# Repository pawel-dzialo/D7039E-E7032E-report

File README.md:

# Report repo for courses D7039E, E7032E, HT22

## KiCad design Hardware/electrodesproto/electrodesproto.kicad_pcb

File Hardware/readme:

All the Hardware design and some simulation files.
The MCU_prototype is fully done with layout
Electrodes_proto is not done in layout preferably it should be done on a 4 layer PCB
but the capabilitys to create a PCB at the schools facilities makes it so It needs to be layed out using only two layer which makes it tough due to all power pins (V+ V-)

In the Simlulations:
Antialiasing,InsAmp,RCfilter is the main steps simulation individually
RC_amp_LP is the steps togheter
IN all sims not the exact components used in the circuitry have a simulation model so an equivalent part is used
but due to this the simulations are not 100% reliable and that why the main testing has been done in the lab.

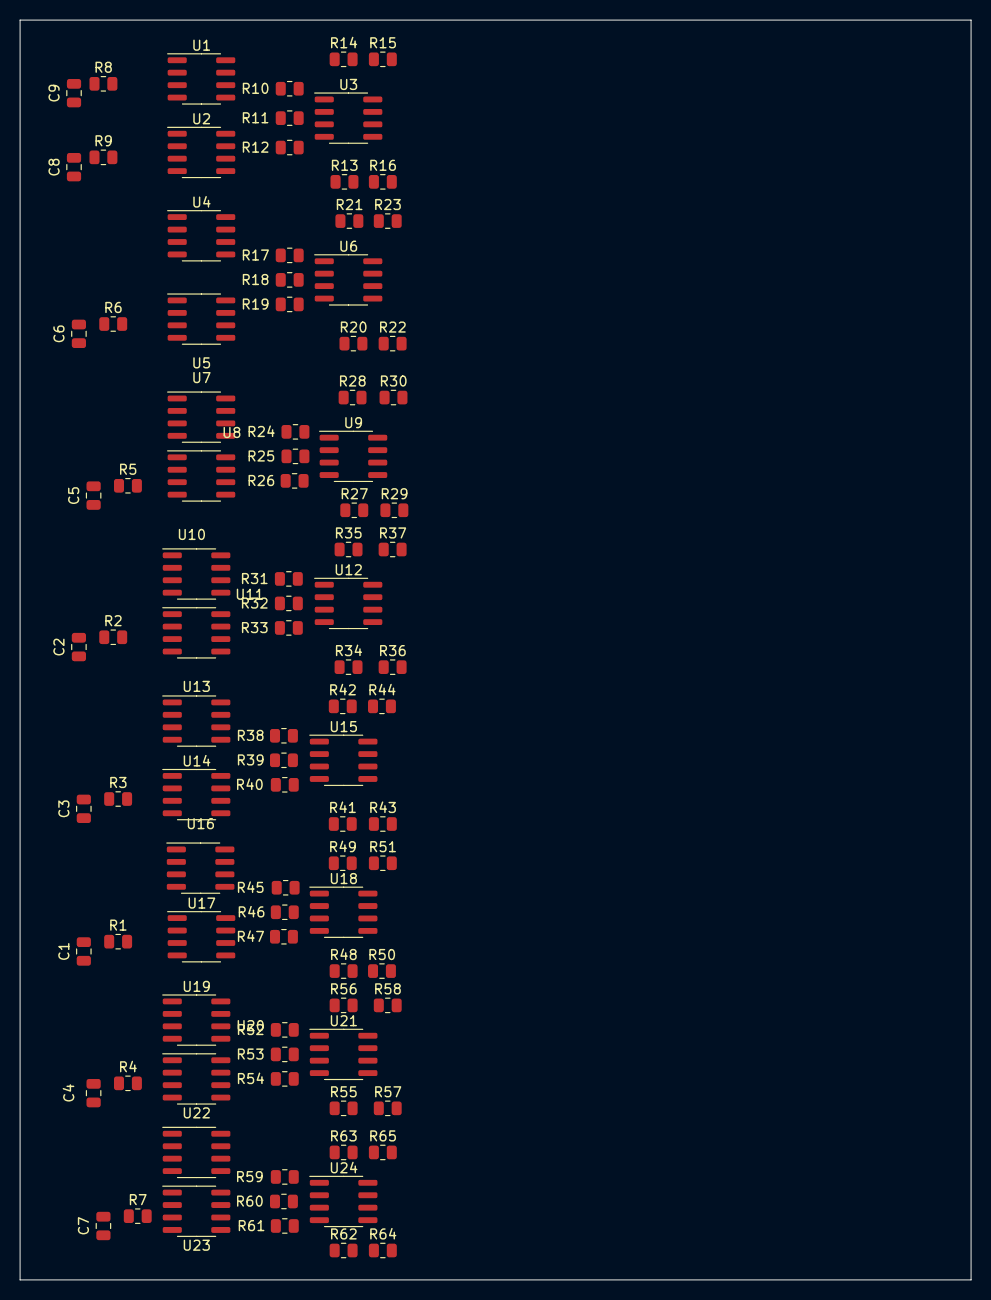
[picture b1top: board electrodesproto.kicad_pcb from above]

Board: 2 copper layers, 97.0 x 128.5 mm, 98 parts (0 on the bottom side), 68 nets, no tracks yet.

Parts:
C1, C2, C3, C4, C5, C6, C7, C8, C9: C; C_0805_2012Metric
R1, R2, R3, R4, R5, R6, R7, R8, R9, R13, R14, R15, R16, R20, R21, R22, R23, R27, R28, R29, R30, R34, R35, R36, R37, R41, R42, R43, R44, R48, R49, R50, R51, R55, R56, R57, R58, R62, R63, R64, R65: R; R_0805_2012Metric
R10, R11, R12, R17, R18, R19, R24, R25, R26, R31, R32, R33, R38, R39, R40, R45, R46, R47, R52, R53, R54, R59, R60, R61: R_Small; R_0805_2012Metric
U1, U2, U3, U4, U5, U6, U7, U8, U9, U10, U11, U12, U13, U14, U15, U16, U17, U18, U19, U20, U21, U22, U23, U24: OPA376xxD; SOIC-8_3.9x4.9mm_P1.27mm

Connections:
E_1: C8.1, R9.2, U2.3 (+)
E_2: C6.1, R6.2, U5.3 (+)
E_3: C5.1, R5.2, U8.3 (+)
E_4: C2.1, R2.2, U11.3 (+)
E_5: C3.1, R3.2, U14.3 (+)
E_6: C1.1, R1.2, U17.3 (+)
E_7: C4.1, R4.2, U20.3 (+)
E_8: C7.1, R7.2, U23.3 (+)
E_OUT_01: R16.2, U3.6
E_OUT_02: R22.2, U6.6
E_OUT_03: R29.2, U9.6
E_OUT_04: R36.2, U12.6
E_OUT_05: R43.2, U15.6
E_OUT_06: R50.2, U18.6
E_OUT_07: R57.2, U21.6
E_OUT_08: R64.2, U24.6
E_ref: C9.1, R8.2, U1.3 (+), U4.3 (+), U7.3 (+), U10.3 (+), U13.3 (+), U16.3 (+), U19.3 (+), U22.3 (+)
GND: C1.2, C2.2, C3.2, C4.2, C5.2, C6.2, C7.2, C8.2, C9.2, R15.2, R23.2, R30.2, R37.2, R44.2, R51.2, R58.2, R65.2
unnamed: R10.1, R14.1, U1.6
unnamed: R10.2, R11.1, U1.2 (-)
unnamed: R11.2, R12.1, U2.2 (-)
unnamed: R12.2, R13.1, U2.6
unnamed: R13.2, R16.1, U3.2 (-)
unnamed: R14.2, R15.1, U3.3 (+)
unnamed: R17.1, R21.1, U4.6
unnamed: R17.2, R18.1, U4.2 (-)
unnamed: R18.2, R19.1, U5.2 (-)
unnamed: R19.2, R20.1, U5.6
unnamed: R20.2, R22.1, U6.2 (-)
unnamed: R21.2, R23.1, U6.3 (+)
unnamed: R24.1, R28.1, U7.6
unnamed: R24.2, R25.1, U7.2 (-)
unnamed: R25.2, R26.1, U8.2 (-)
unnamed: R26.2, R27.1, U8.6
unnamed: R27.2, R29.1, U9.2 (-)
unnamed: R28.2, R30.1, U9.3 (+)
unnamed: R31.1, R35.1, U10.6
unnamed: R31.2, R32.1, U10.2 (-)
unnamed: R32.2, R33.1, U11.2 (-)
unnamed: R33.2, R34.1, U11.6
unnamed: R34.2, R36.1, U12.2 (-)
unnamed: R35.2, R37.1, U12.3 (+)
unnamed: R38.1, R42.1, U13.6
unnamed: R38.2, R39.1, U13.2 (-)
unnamed: R39.2, R40.1, U14.2 (-)
unnamed: R40.2, R41.1, U14.6
unnamed: R41.2, R43.1, U15.2 (-)
unnamed: R42.2, R44.1, U15.3 (+)
unnamed: R45.1, R49.1, U16.6
unnamed: R45.2, R46.1, U16.2 (-)
unnamed: R46.2, R47.1, U17.2 (-)
unnamed: R47.2, R48.1, U17.6
unnamed: R48.2, R50.1, U18.2 (-)
unnamed: R49.2, R51.1, U18.3 (+)
unnamed: R52.1, R56.1, U19.6
unnamed: R52.2, R53.1, U19.2 (-)
unnamed: R53.2, R54.1, U20.2 (-)
unnamed: R54.2, R55.1, U20.6
unnamed: R55.2, R57.1, U21.2 (-)
unnamed: R56.2, R58.1, U21.3 (+)
unnamed: R59.1, R63.1, U22.6
unnamed: R59.2, R60.1, U22.2 (-)
unnamed: R60.2, R61.1, U23.2 (-)
unnamed: R61.2, R62.1, U23.6
unnamed: R62.2, R64.1, U24.2 (-)
unnamed: R63.2, R65.1, U24.3 (+)
V+: U1.7 (V+), U2.7 (V+), U3.7 (V+), U4.7 (V+), U5.7 (V+), U6.7 (V+), U7.7 (V+), U8.7 (V+), U9.7 (V+), U10.7 (V+), U11.7 (V+), U12.7 (V+), U13.7 (V+), U14.7 (V+), U15.7 (V+), U16.7 (V+), U17.7 (V+), U18.7 (V+), U19.7 (V+), U20.7 (V+), U21.7 (V+), U22.7 (V+), U23.7 (V+), U24.7 (V+)
V-: U1.4 (V-), U2.4 (V-), U3.4 (V-), U4.4 (V-), U5.4 (V-), U6.4 (V-), U7.4 (V-), U8.4 (V-), U9.4 (V-), U10.4 (V-), U11.4 (V-), U12.4 (V-), U13.4 (V-), U14.4 (V-), U15.4 (V-), U16.4 (V-), U17.4 (V-), U18.4 (V-), U19.4 (V-), U20.4 (V-), U21.4 (V-), U22.4 (V-), U23.4 (V-), U24.4 (V-)

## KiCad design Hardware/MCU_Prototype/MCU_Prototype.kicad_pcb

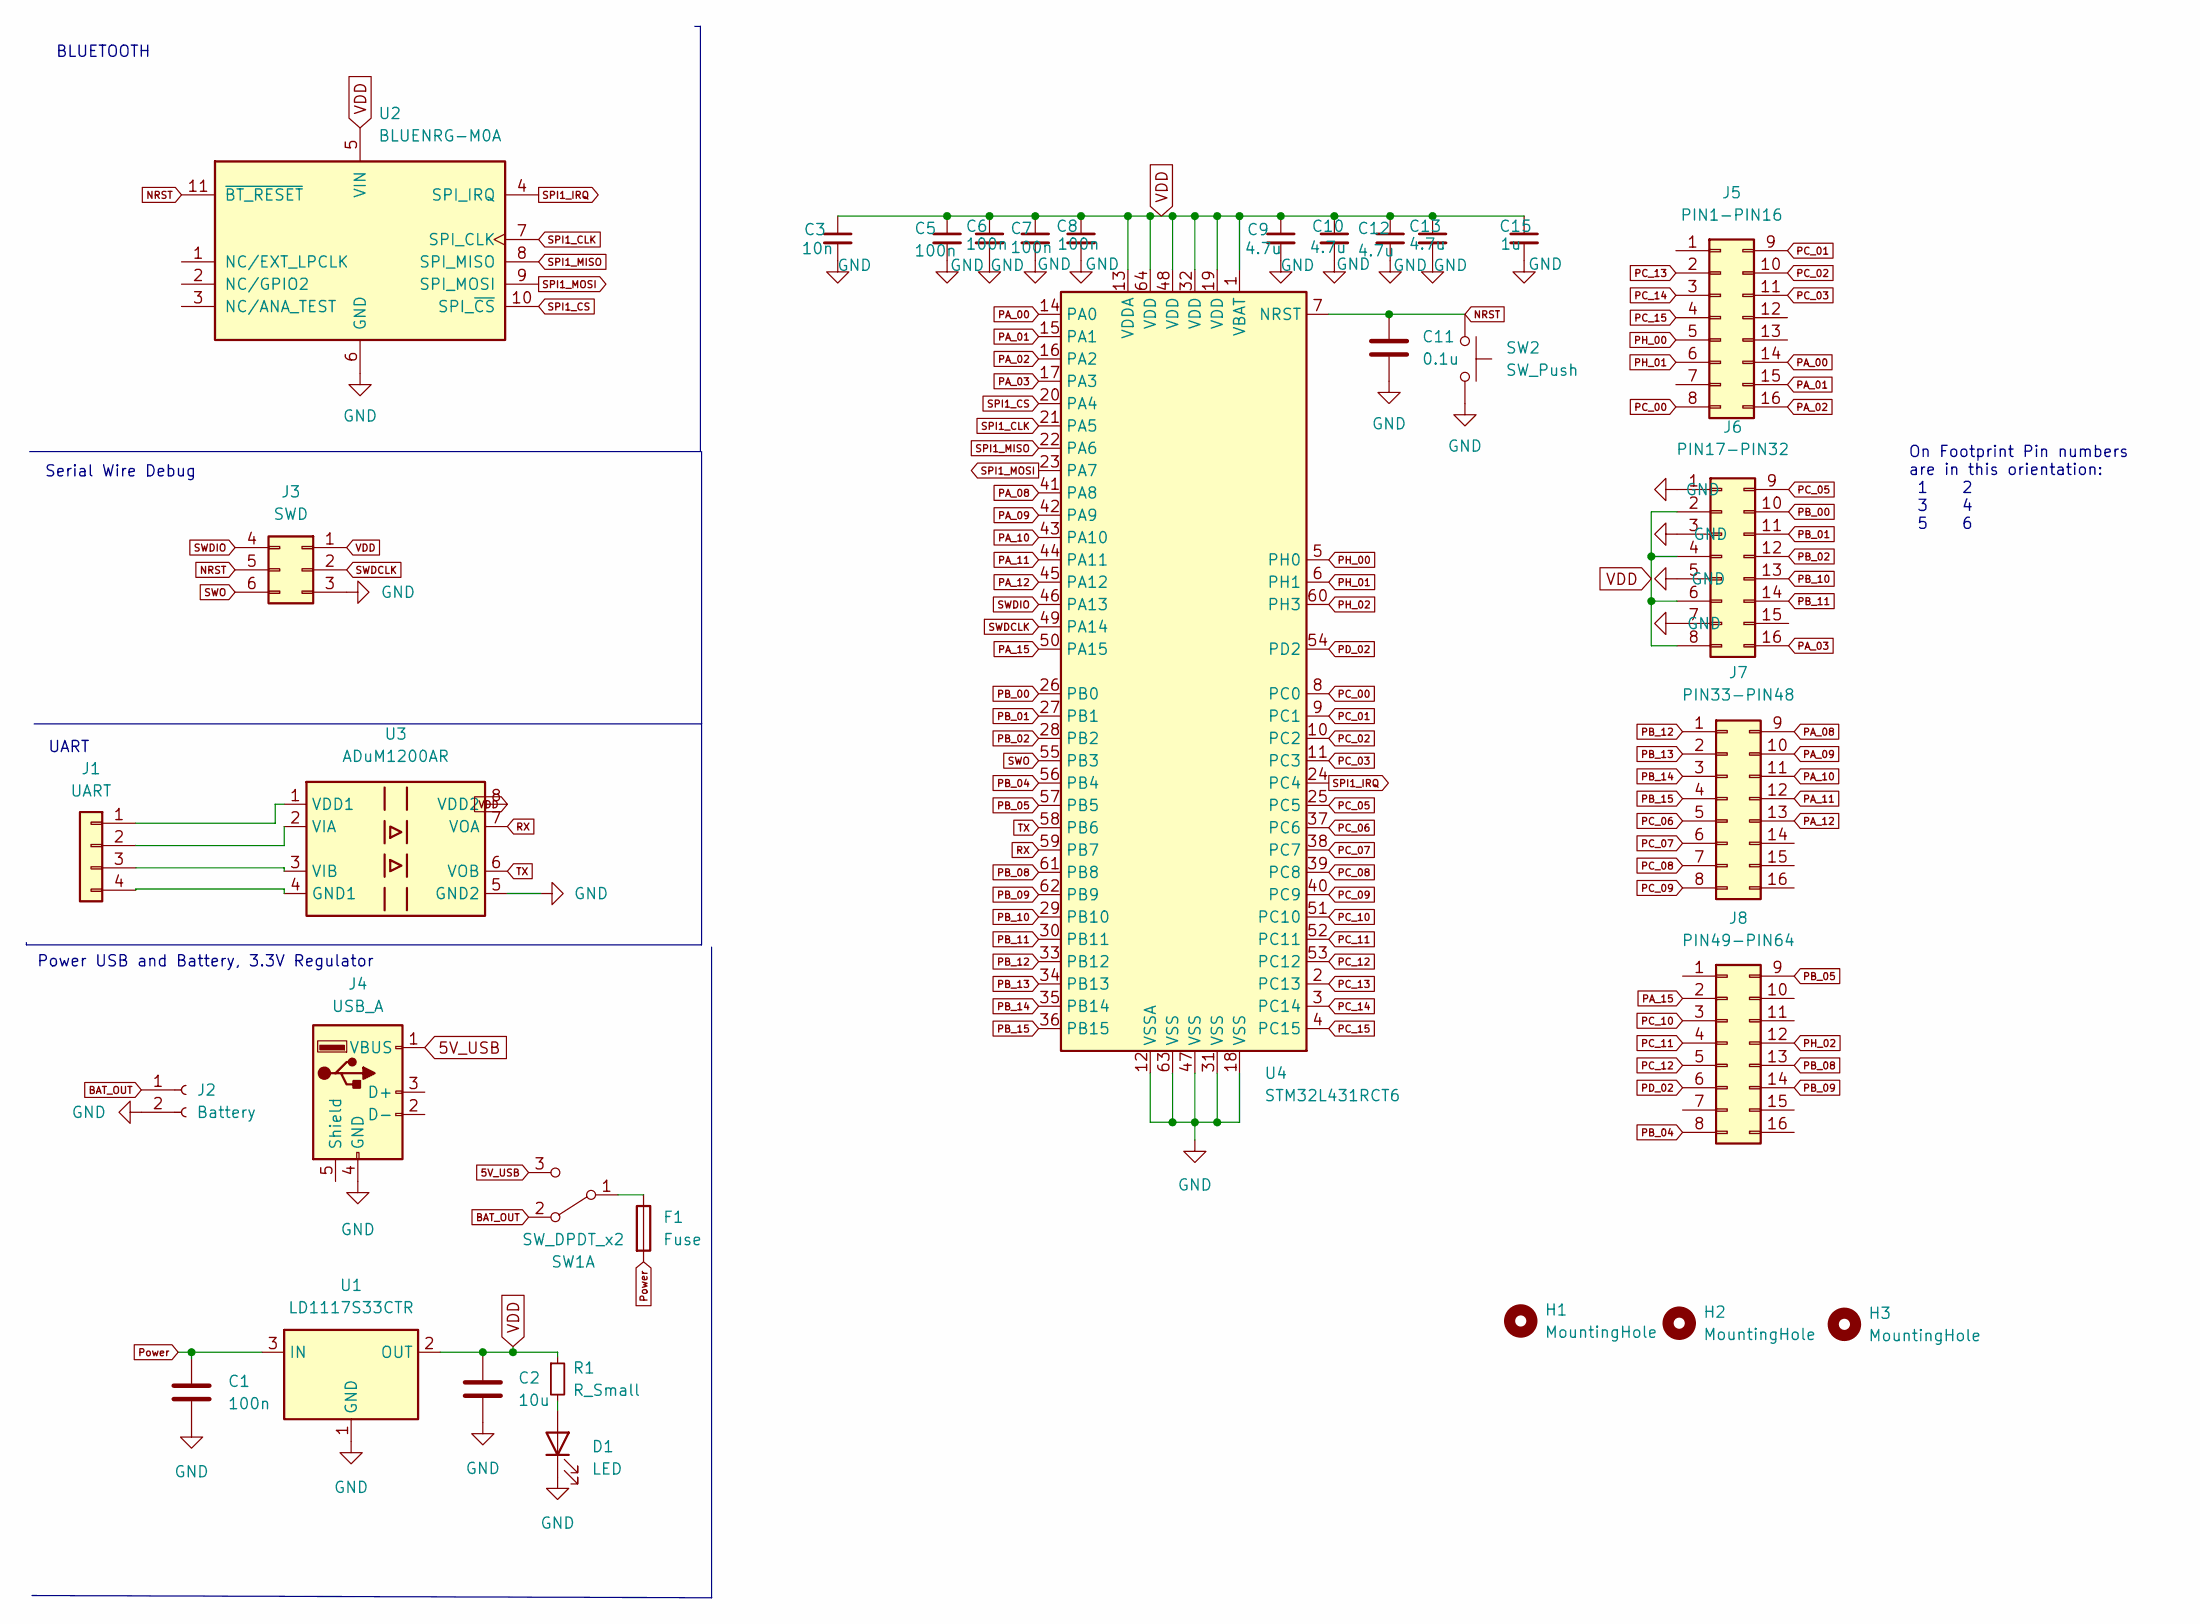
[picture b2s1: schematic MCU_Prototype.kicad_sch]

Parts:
C1, C5, C6, C7, C8: 100n; C_0805_2012Metric
C2: 10u; CP_Radial_D5.0mm_P2.00mm
C3: 10n; C_0805_2012Metric
C9, C10, C12, C13: 4.7u; CP_Radial_D5.0mm_P2.00mm
C11: 0.1u; C_0805_2012Metric
C15: 1u; CP_Radial_D5.0mm_P2.00mm
D1: LED
F1: Fuse; Fuse_Rad
H1, H2, H3: MountingHole; MountingHole_3.2mm_M3_DIN965_Pad
J1: UART; PinHeader_1x04_P2.54mm_Vertical
J2: Battery; JST_PH_S2B-PH-K_1x02_P2.00mm_Horizontal
J3: SWD; PinHeader_1x06_P2.54mm_Vertical
J4: USB_A; USBA
J5: PIN1-PIN16; PinHeader_2x08_P2.54mm_Vertical
J6: PIN17-PIN32; PinHeader_2x08_P2.54mm_Vertical
J7: PIN33-PIN48; PinHeader_2x08_P2.54mm_Vertical
J8: PIN49-PIN64; PinHeader_2x08_P2.54mm_Vertical
R1: R_Small; R_0805_2012Metric
SW1: SW_DPDT_x2; Switch
SW2: SW_Push; Button
U1: LD1117S33CTR; SOT223
U2: BLUENRG-M0A; ST_SPBTLE
U3: ADuM1200AR; SOIC127P600X175-8N
U4: STM32L431RCT6; LQFP-64_10x10mm_P0.5mm

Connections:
5V_USB: J4.1 (VBUS), SW1.3 (C)
BAT_OUT: J2.1, SW1.2 (A)
GND: C1.2, C2.2, C3.2, C5.2, C6.2, C7.2, C8.2, C9.2, C10.2, C11.2, C12.2, C13.2, C15.2, D1.1 (K), J2.2, J3.3, J4.4 (GND), J6.1, J6.3, J6.5, J6.7, SW2.2, U1.1 (GND), U1.5 (GND), U2.6 (GND), U3.5 (GND2), U4.12 (VSSA), U4.18 (VSS), U4.31 (VSS), U4.47 (VSS), U4.63 (VSS)
NRST: C11.1, J3.5, SW2.1, U2.11 (~BT_RESET), U4.7 (NRST)
unnamed: D1.2 (A), R1.2
unnamed: F1.1, SW1.1 (B)
unnamed: J1.1, U3.1 (VDD1)
unnamed: J1.2, U3.2 (VIA)
unnamed: J1.3, U3.3 (VIB)
unnamed: J1.4, U3.4 (GND1)
PA_00: J5.14, U4.14 (PA0)
PA_01: J5.15, U4.15 (PA1)
PA_02: J5.16, U4.16 (PA2)
PA_03: J6.16, U4.17 (PA3)
PA_08: J7.9, U4.41 (PA8)
PA_09: J7.10, U4.42 (PA9)
PA_10: J7.11, U4.43 (PA10)
PA_11: J7.12, U4.44 (PA11)
PA_12: J7.13, U4.45 (PA12)
PA_15: J8.2, U4.50 (PA15)
PB_00: J6.10, U4.26 (PB0)
PB_01: J6.11, U4.27 (PB1)
PB_02: J6.12, U4.28 (PB2)
PB_04: J8.8, U4.56 (PB4)
PB_05: J8.9, U4.57 (PB5)
PB_08: J8.13, U4.61 (PB8)
PB_09: J8.14, U4.62 (PB9)
PB_10: J6.13, U4.29 (PB10)
PB_11: J6.14, U4.30 (PB11)
PB_12: J7.1, U4.33 (PB12)
PB_13: J7.2, U4.34 (PB13)
PB_14: J7.3, U4.35 (PB14)
PB_15: J7.4, U4.36 (PB15)
PC_00: J5.8, U4.8 (PC0)
PC_01: J5.9, U4.9 (PC1)
PC_02: J5.10, U4.10 (PC2)
PC_03: J5.11, U4.11 (PC3)
PC_05: J6.9, U4.25 (PC5)
PC_06: J7.5, U4.37 (PC6)
PC_07: J7.6, U4.38 (PC7)
PC_08: J7.7, U4.39 (PC8)
PC_09: J7.8, U4.40 (PC9)
PC_10: J8.3, U4.51 (PC10)
PC_11: J8.4, U4.52 (PC11)
PC_12: J8.5, U4.53 (PC12)
PC_13: J5.2, U4.2 (PC13)
PC_14: J5.3, U4.3 (PC14)
PC_15: J5.4, U4.4 (PC15)
PD_02: J8.6, U4.54 (PD2)
PH_00: J5.5, U4.5 (PH0)
PH_01: J5.6, U4.6 (PH1)
PH_02: J8.12, U4.60 (PH3)
Power: C1.1, F1.2, U1.3 (IN)
RX: U3.7 (VOA), U4.59 (PB7)
SPI1_CLK: U2.7 (SPI_CLK), U4.21 (PA5)
SPI1_CS: U2.10 (SPI_~CS), U4.20 (PA4)
SPI1_IRQ: U2.4 (SPI_IRQ), U4.24 (PC4)
SPI1_MISO: U2.8 (SPI_MISO), U4.22 (PA6)
SPI1_MOSI: U2.9 (SPI_MOSI), U4.23 (PA7)
SWDCLK: J3.2, U4.49 (PA14)
SWDIO: J3.4, U4.46 (PA13)
SWO: J3.6, U4.55 (PB3)
TX: U3.6 (VOB), U4.58 (PB6)
VDD: C2.1, C3.1, C5.1, C6.1, C7.1, C8.1, C9.1, C10.1, C12.1, C13.1, C15.1, J3.1, J6.2, J6.4, J6.6, J6.8, R1.1, U1.2 (OUT), U2.5 (VIN), U3.8 (VDD2), U4.1 (VBAT), U4.13 (VDDA), U4.19 (VDD), U4.32 (VDD), U4.48 (VDD), U4.64 (VDD)

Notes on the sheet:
UART
BLUETOOTH
Serial Wire Debug
Power USB and Battery, 3.3V Regulator
On Footprint Pin numbers are in this orientation: 1 2 3 4 5 6

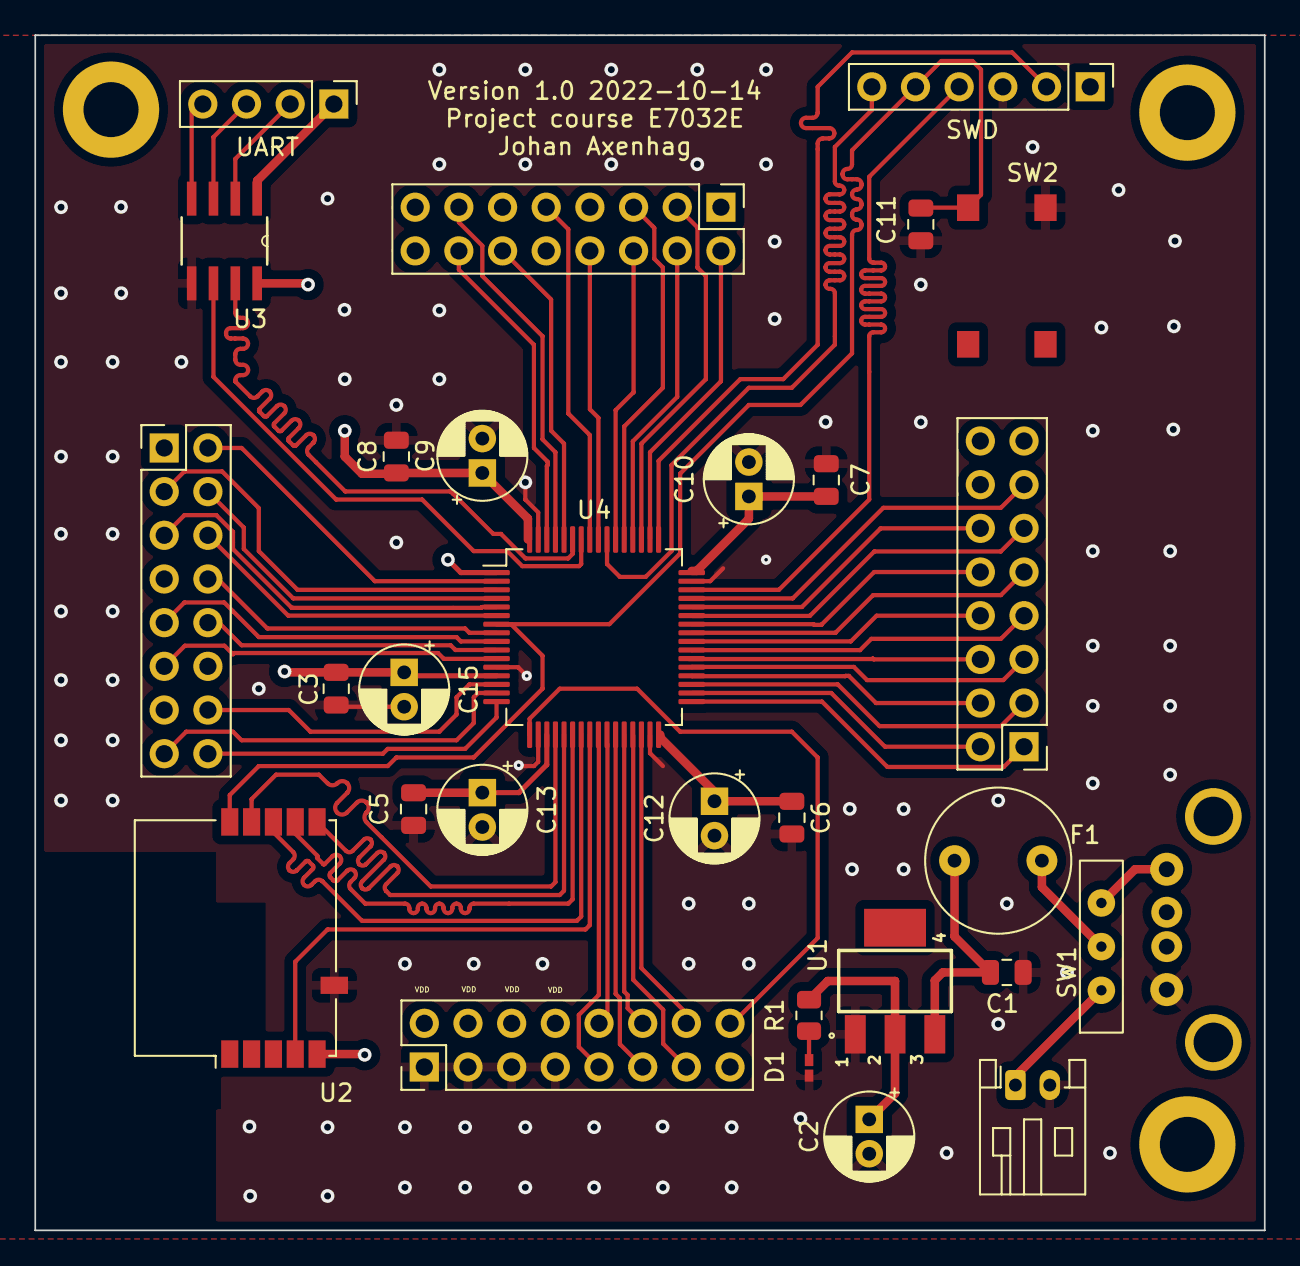
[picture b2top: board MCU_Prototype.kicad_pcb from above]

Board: 4 copper layers, 71.5 x 69.5 mm, 33 parts (0 on the bottom side), 64 nets.

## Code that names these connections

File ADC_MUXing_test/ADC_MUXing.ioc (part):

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Mcu.Name=STM32L4S5VITx
Mcu.Package=LQFP100
Mcu.UserName=STM32L4S5VITx
PA0.GPIOParameters=GPIO_ModeDefaultPP,GPIO_Speed,GPIO_PuPd,GPIO_Label
PA0.GPIO_Label=ARD_D1 [UART4_TX]
PA0.GPIO_ModeDefaultPP=GPIO_MODE_AF_PP
PA0.GPIO_PuPd=GPIO_NOPULL
PA0.GPIO_Speed=GPIO_SPEED_FREQ_VERY_HIGH
PA0.Mode=Asynchronous
PA0.Signal=UART4_TX
PA1.GPIOParameters=GPIO_ModeDefaultPP,GPIO_Speed,GPIO_PuPd,GPIO_Label
PA1.GPIO_Label=ARD_D0 [UART4_RX]
PA1.GPIO_ModeDefaultPP=GPIO_MODE_AF_PP
PA1.GPIO_PuPd=GPIO_NOPULL
PA1.GPIO_Speed=GPIO_SPEED_FREQ_VERY_HIGH
PA1.Mode=Asynchronous
PA1.Signal=UART4_RX
PA10.GPIOParameters=GPIO_Label
PA10.GPIO_Label=USB_OTG_FS_ID
PA10.Mode=OTG/Dual_Role_Device
PA10.Signal=USB_OTG_FS_ID
PA11.GPIOParameters=GPIO_Label
PA11.GPIO_Label=USB_OTG_FS_DM
PA11.Mode=OTG/Dual_Role_Device
PA11.Signal=USB_OTG_FS_DM
PA12.GPIOParameters=GPIO_Label
PA12.GPIO_Label=USB_OTG_FS_DP
PA12.Mode=OTG/Dual_Role_Device
PA12.Signal=USB_OTG_FS_DP
PA13\ (JTMS/SWDIO).GPIOParameters=GPIO_Label
PA13\ (JTMS/SWDIO).GPIO_Label=SYS_JTMS_SWDIO
PA13\ (JTMS/SWDIO).Mode=Serial_Wire
PA13\ (JTMS/SWDIO).Signal=SYS_JTMS-SWDIO
PA14\ (JTCK/SWCLK).GPIOParameters=GPIO_Label
PA14\ (JTCK/SWCLK).GPIO_Label=SYS_JTCK_SWCLK
PA14\ (JTCK/SWCLK).Mode=Serial_Wire
PA14\ (JTCK/SWCLK).Signal=SYS_JTCK-SWCLK
PA15\ (JTDI).GPIOParameters=GPIO_Speed,PinState,GPIO_PuPd,GPIO_Label,GPIO_ModeDefaultOutputPP
PA15\ (JTDI).GPIO_Label=ARD_D9
PA15\ (JTDI).GPIO_ModeDefaultOutputPP=GPIO_MODE_OUTPUT_PP
PA15\ (JTDI).GPIO_PuPd=GPIO_NOPULL
PA15\ (JTDI).GPIO_Speed=GPIO_SPEED_FREQ_LOW
PA15\ (JTDI).PinState=GPIO_PIN_RESET
PA15\ (JTDI).Signal=GPIO_Output
PA2.GPIOParameters=GPIO_Speed,PinState,GPIO_PuPd,GPIO_Label,GPIO_ModeDefaultOutputPP
PA2.GPIO_Label=ARD_D10 [SPI_SSN]
PA2.GPIO_ModeDefaultOutputPP=GPIO_MODE_OUTPUT_PP
PA2.GPIO_PuPd=GPIO_NOPULL
PA2.GPIO_Speed=GPIO_SPEED_FREQ_LOW
PA2.PinState=GPIO_PIN_RESET
PA2.Signal=GPIO_Output
PA3.GPIOParameters=GPIO_Label
PA3.GPIO_Label=ARD_D4
PA3.Signal=GPIO_Output
PA4.GPIOParameters=GPIO_Label,GPIO_ModeDefaultEXTI
PA4.GPIO_Label=D7
PA4.GPIO_ModeDefaultEXTI=GPIO_MODE_IT_FALLING
PA4.Signal=GPXTI4
PA5.GPIOParameters=GPIO_Speed,GPIO_PuPd,GPIO_Label,GPIO_Mode
PA5.GPIO_Label=ARD_D13 [SPI1_SCK/LED1]
PA5.GPIO_Mode=GPIO_MODE_AF_PP
PA5.GPIO_PuPd=GPIO_NOPULL
PA5.GPIO_Speed=GPIO_SPEED_FREQ_VERY_HIGH
PA5.Mode=Full_Duplex_Master
PA5.Signal=SPI1_SCK
PA6.GPIOParameters=GPIO_Speed,GPIO_PuPd,GPIO_Label,GPIO_Mode
PA6.GPIO_Label=ARD_D12 [SPI1_MISO]
PA6.GPIO_Mode=GPIO_MODE_AF_PP
PA6.GPIO_PuPd=GPIO_NOPULL
PA6.GPIO_Speed=GPIO_SPEED_FREQ_VERY_HIGH
PA6.Mode=Full_Duplex_Master
PA6.Signal=SPI1_MISO
PA7.GPIOParameters=GPIO_Speed,GPIO_PuPd,GPIO_Label,GPIO_Mode
PA7.GPIO_Label=ARD_D11 [SPI1_MOSI]
PA7.GPIO_Mode=GPIO_MODE_AF_PP
PA7.GPIO_PuPd=GPIO_NOPULL
PA7.GPIO_Speed=GPIO_SPEED_FREQ_VERY_HIGH
PA7.Mode=Full_Duplex_Master
PA7.Signal=SPI1_MOSI
PA8.GPIOParameters=GPIO_Speed,PinState,GPIO_PuPd,GPIO_Label,GPIO_ModeDefaultOutputPP
PA8.GPIO_Label=SPBTLE_RF_RST
PA8.GPIO_ModeDefaultOutputPP=GPIO_MODE_OUTPUT_PP
PA8.GPIO_PuPd=GPIO_NOPULL
PA8.GPIO_Speed=GPIO_SPEED_FREQ_LOW
PA8.PinState=GPIO_PIN_RESET
PA8.Signal=GPIO_Output
PA9.GPIOParameters=GPIO_PuPd,GPIO_Label,GPIO_Mode
PA9.GPIO_Label=USB_OTG_FS_VBUS
PA9.GPIO_Mode=GPIO_MODE_INPUT
PA9.GPIO_PuPd=GPIO_NOPULL
PA9.Mode=Activate_VBUS
PA9.Signal=USB_OTG_FS_VBUS
PB0.GPIOParameters=GPIO_PuPd,GPIO_Label,GPIO_ModeDefaultEXTI
PB0.GPIO_Label=ARD_D3 [INT_EXT10]
PB0.GPIO_ModeDefaultEXTI=GPIO_MODE_IT_RISING
PB0.GPIO_PuPd=GPIO_NOPULL
PB0.Signal=GPXTI0
PB1.GPIOParameters=GPIO_Speed,GPIO_Label
PB1.GPIO_Label=ARD_D6
PB1.GPIO_Speed=GPIO_SPEED_FREQ_VERY_HIGH
PB1.Signal=S_TIM3_CH4
PB10.GPIOParameters=GPIO_Speed,GPIO_Label,GPIO_Pu,GPIO_Mode
PB10.GPIO_Label=INTERNAL_I2C2_SCL [MEMs]
PB10.GPIO_Mode=GPIO_MODE_AF_OD
PB10.GPIO_Pu=GPIO_PULLUP
PB10.GPIO_Speed=GPIO_SPEED_FREQ_VERY_HIGH
PB10.Mode=I2C
PB10.Signal=I2C2_SCL
PB11.GPIOParameters=GPIO_Speed,GPIO_Label,GPIO_Pu,GPIO_Mode
PB11.GPIO_Label=INTERNAL_I2C2_SDA [MEMs]
PB11.GPIO_Mode=GPIO_MODE_AF_OD
PB11.GPIO_Pu=GPIO_PULLUP
PB11.GPIO_Speed=GPIO_SPEED_FREQ_VERY_HIGH
PB11.Mode=I2C
PB11.Signal=I2C2_SDA
PB12.GPIOParameters=GPIO_Speed,PinState,GPIO_PuPd,GPIO_Label,GPIO_ModeDefaultOutputPP
PB12.GPIO_Label=ISM43362_BOOT0
PB12.GPIO_ModeDefaultOutputPP=GPIO_MODE_OUTPUT_PP
PB12.GPIO_PuPd=GPIO_NOPULL
PB12.GPIO_Speed=GPIO_SPEED_FREQ_LOW
PB12.PinState=GPIO_PIN_RESET
PB12.Signal=GPIO_Output
PB13.GPIOParameters=GPIO_Speed,PinState,GPIO_PuPd,GPIO_Label,GPIO_ModeDefaultOutputPP
PB13.GPIO_Label=ISM43362_WAKEUP
PB13.GPIO_ModeDefaultOutputPP=GPIO_MODE_OUTPUT_PP
PB13.GPIO_PuPd=GPIO_NOPULL
PB13.GPIO_Speed=GPIO_SPEED_FREQ_LOW
PB13.PinState=GPIO_PIN_RESET
PB13.Signal=GPIO_Output
PB14.GPIOParameters=GPIO_Speed,PinState,GPIO_PuPd,GPIO_Label,GPIO_ModeDefaultOutputPP
PB14.GPIO_Label=LED2 [LED_GREEN]
PB14.GPIO_ModeDefaultOutputPP=GPIO_MODE_OUTPUT_PP
PB14.GPIO_PuPd=GPIO_NOPULL
PB14.GPIO_Speed=GPIO_SPEED_FREQ_LOW
PB14.PinState=GPIO_PIN_RESET
PB14.Signal=GPIO_Output
PB15.GPIOParameters=GPIO_Label
PB15.GPIO_Label=SPSGRF_915_SDN [SPSGRF_SDN]
PB15.Signal=GPIO_Output
PB2.GPIOParameters=GPIO_Speed,PinState,GPIO_PuPd,GPIO_Label,GPIO_ModeDefaultOutputPP
PB2.GPIO_Label=ARD_D8
PB2.GPIO_ModeDefaultOutputPP=GPIO_MODE_OUTPUT_PP
PB2.GPIO_PuPd=GPIO_NOPULL
PB2.GPIO_Speed=GPIO_SPEED_FREQ_LOW
PB2.PinState=GPIO_PIN_RESET
PB2.Signal=GPIO_Output
PB3\ (JTDO/TRACESWO).GPIOParameters=GPIO_Label
PB3\ (JTDO/TRACESWO).GPIO_Label=SYS_JTD0_SWO
PB3\ (JTDO/TRACESWO).Signal=SYS_JTDO-SWO
PB4\ (NJTRST).GPIOParameters=GPIO_Speed,PinState,GPIO_PuPd,GPIO_Label,GPIO_ModeDefaultOutputPP
PB4\ (NJTRST).GPIO_Label=ARD_D5
PB4\ (NJTRST).GPIO_ModeDefaultOutputPP=GPIO_MODE_OUTPUT_PP
PB4\ (NJTRST).GPIO_PuPd=GPIO_NOPULL
PB4\ (NJTRST).GPIO_Speed=GPIO_SPEED_FREQ_LOW
PB4\ (NJTRST).PinState=GPIO_PIN_RESET
PB4\ (NJTRST).Signal=GPIO_Output
PB5.GPIOParameters=GPIO_Label
PB5.GPIO_Label=SPSGRF_915_SPI3_CSN [SPSGRF_SPI_CS]
PB5.Signal=GPIO_Output
PB6.GPIOParameters=GPIO_ModeDefaultPP,GPIO_Speed,GPIO_FM6,GPIO_PuPd,GPIO_Label
PB6.GPIO_FM6=__NULL
PB6.GPIO_Label=ST-LINK-UART1_TX
PB6.GPIO_ModeDefaultPP=GPIO_MODE_AF_PP
PB6.GPIO_PuPd=GPIO_NOPULL
PB6.GPIO_Speed=GPIO_SPEED_FREQ_VERY_HIGH
PB6.Mode=Asynchronous
PB6.Signal=USART1_TX
PB7.GPIOParameters=GPIO_ModeDefaultPP,GPIO_Speed,GPIO_PuPd,GPIO_Label,GPIO_FM7
PB7.GPIO_FM7=__NULL
PB7.GPIO_Label=ST_LINK_UART1_RX
PB7.GPIO_ModeDefaultPP=GPIO_MODE_AF_PP
PB7.GPIO_PuPd=GPIO_NOPULL
PB7.GPIO_Speed=GPIO_SPEED_FREQ_VERY_HIGH
PB7.Mode=Asynchronous
PB7.Signal=USART1_RX
PB8.GPIOParameters=GPIO_Speed,GPIO_Label,GPIO_FM8,GPIO_Pu,GPIO_Mode
PB8.GPIO_FM8=__NULL
PB8.GPIO_Label=ARD_D15 [I2C1_SCL]
PB8.GPIO_Mode=GPIO_MODE_AF_OD
PB8.GPIO_Pu=GPIO_PULLUP
PB8.GPIO_Speed=GPIO_SPEED_FREQ_VERY_HIGH
PB8.Mode=I2C
PB8.Signal=I2C1_SCL
PB9.GPIOParameters=GPIO_Speed,GPIO_Label,GPIO_Pu,GPIO_Mode,GPIO_FM9
PB9.GPIO_FM9=__NULL
PB9.GPIO_Label=ARD_D14 [I2C1_SDA]
PB9.GPIO_Mode=GPIO_MODE_AF_OD
PB9.GPIO_Pu=GPIO_PULLUP
PB9.GPIO_Speed=GPIO_SPEED_FREQ_VERY_HIGH
PB9.Mode=I2C
PB9.Signal=I2C1_SDA
PC0.GPIOParameters=GPIO_Speed,PinState
PC0.GPIO_Speed=GPIO_SPEED_FREQ_VERY_HIGH
PC0.PinState=GPIO_PIN_RESET
PC0.Signal=GPIO_Output
PC1.GPIOParameters=GPIO_Speed,PinState
PC1.GPIO_Speed=GPIO_SPEED_FREQ_VERY_HIGH
PC1.PinState=GPIO_PIN_RESET
PC1.Signal=GPIO_Output
PC10.GPIOParameters=GPIO_Speed,GPIO_PuPd,GPIO_Label,GPIO_Mode
PC10.GPIO_Label=INTERNAL-SPI3_SCK [BT module_SPI_MOSI] [ISM43362_MOSI]
PC10.GPIO_Mode=GPIO_MODE_AF_PP
PC10.GPIO_PuPd=GPIO_NOPULL
PC10.GPIO_Speed=GPIO_SPEED_FREQ_VERY_HIGH
PC10.Mode=Full_Duplex_Master
PC10.Signal=SPI3_SCK
PC11.GPIOParameters=GPIO_Speed,GPIO_PuPd,GPIO_Label,GPIO_Mode
PC11.GPIO_Label=INTERNAL_SPI3_MISO [BT module_SPI_MOSI] [ISM43362_MOSI]
PC11.GPIO_Mode=GPIO_MODE_AF_PP
PC11.GPIO_PuPd=GPIO_NOPULL
PC11.GPIO_Speed=GPIO_SPEED_FREQ_VERY_HIGH
PC11.Mode=Full_Duplex_Master
PC11.Signal=SPI3_MISO
PC12.GPIOParameters=GPIO_Speed,GPIO_PuPd,GPIO_Label,GPIO_Mode
PC12.GPIO_Label=INTERNAL_SPI3_MOSI [BT module_SPI_MOSI] [ISM43362_MOSI]
PC12.GPIO_Mode=GPIO_MODE_AF_PP
PC12.GPIO_PuPd=GPIO_NOPULL
PC12.GPIO_Speed=GPIO_SPEED_FREQ_VERY_HIGH
PC12.Mode=Full_Duplex_Master
PC12.Signal=SPI3_MOSI
PC13.GPIOParameters=GPIO_PuPd,GPIO_Label,GPIO_ModeDefaultEXTI
PC13.GPIO_Label=BUTTON_EXTI13 [B2]
PC13.GPIO_ModeDefaultEXTI=GPIO_MODE_IT_RISING
PC13.GPIO_PuPd=GPIO_NOPULL
PC13.Signal=GPXTI13
PC14-OSC32_IN\ (PC14).Mode=LSE-External-Oscillator
PC14-OSC32_IN\ (PC14).Signal=RCC_OSC32_IN
PC15-OSC32_OUT\ (PC15).Mode=LSE-External-Oscillator
PC15-OSC32_OUT\ (PC15).Signal=RCC_OSC32_OUT
PC2.GPIOParameters=GPIO_Speed
PC2.GPIO_Speed=GPIO_SPEED_FREQ_VERY_HIGH
PC2.Signal=GPIO_Output
PC3.GPIOParameters=GPIO_Speed
PC3.GPIO_Speed=GPIO_SPEED_FREQ_VERY_HIGH
PC3.Signal=GPIO_Output
PC4.GPIOParameters=GPIO_PuPd,GPIO_Label,GPIO_Mode
PC4.GPIO_Label=ARD_A1 [ADC]
PC4.GPIO_Mode=GPIO_MODE_ANALOG_ADC_CONTROL
PC4.GPIO_PuPd=GPIO_NOPULL
PC4.Signal=ADCx_IN13
PC5.GPIOParameters=GPIO_PuPd,GPIO_Label,GPIO_Mode
PC5.GPIO_Label=ARD_A0 [ADC]
PC5.GPIO_Mode=GPIO_MODE_ANALOG_ADC_CONTROL
PC5.GPIO_PuPd=GPIO_NOPULL
PC5.Signal=ADCx_IN14

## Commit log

2022-09-04 Lagt till en enkel git-guide
2022-09-04 Lagt till min sammanfattning
2022-09-04 lagt till en liten git-guide
2022-09-05 små ändringar i git-guide
2022-09-11 Laddat upp sammanfattning av två av de jag läst.
2022-09-11 Add files via upload
    Klar med min ena artikel
2022-09-16 Add files via upload
    Gjorde en snabb draft av ett latex document till rapporten
2022-09-19 added my log
2022-09-19 Added my Logg
2022-09-20 Updated log
2022-09-20 Create Michelle_log
2022-09-20 Rename Michelle_log to Michelle_log.txt
2022-09-24 Updated JohanL_logg
2022-09-25 La till Johan A logg
2022-09-25 Uppdaterat Johan A logg
2022-09-28 worked on introduction and dataset
2022-09-28 Updated log file
2022-09-30 Update 4-Theory.tex
    Added a subsection about epileptic seizures, with citations.
2022-09-30 Update 5-Method.tex
    Added a signal processing subsection, with citations.
2022-09-30 Added a flow diagram of our project method
2022-10-03 Added a updated flow chart
2022-11-06 Update Fabian_log.txt
    update
2022-11-06 Add files via upload
    Has to come with a data folder in order to work, but that one is currently a bit too big to have in github. Also has no direct input on what data to use, so it relies on hardcoding for that, which ma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
2022-11-07 Create Filter and artifact removal (python)
2022-11-07 Create CIC decimation (C)
2022-11-08 Update and rename CIC decimation (C) to CIC dec with FIR comp (C)
2022-12-05 Add files via upload
    Code for extracting a pattern for a spike in EEG data, The filter needs to be applied, but error arises, dont know why, Michele plz help
2022-12-12 updated log for the last month
2022-12-19 Add files via upload
    Least square baserat matched filter, har med pattern extraction biten men den kan lätt tas bort.
2023-01-24 Pushing the interesting parts of the code i've written during the project
2023-01-24 Formatting
2023-01-24 Fixing last commit
2023-01-24 Added code for testing the multiplexing and signal collection
2023-01-24 Added rest of the simulator code
2023-01-24 Fixed formatting
2023-01-24 Updated report to current version from Overleaf
2023-01-25 Update Fabian_log.txt
    christmas notes
2023-01-25 Add files via upload
    latest update
